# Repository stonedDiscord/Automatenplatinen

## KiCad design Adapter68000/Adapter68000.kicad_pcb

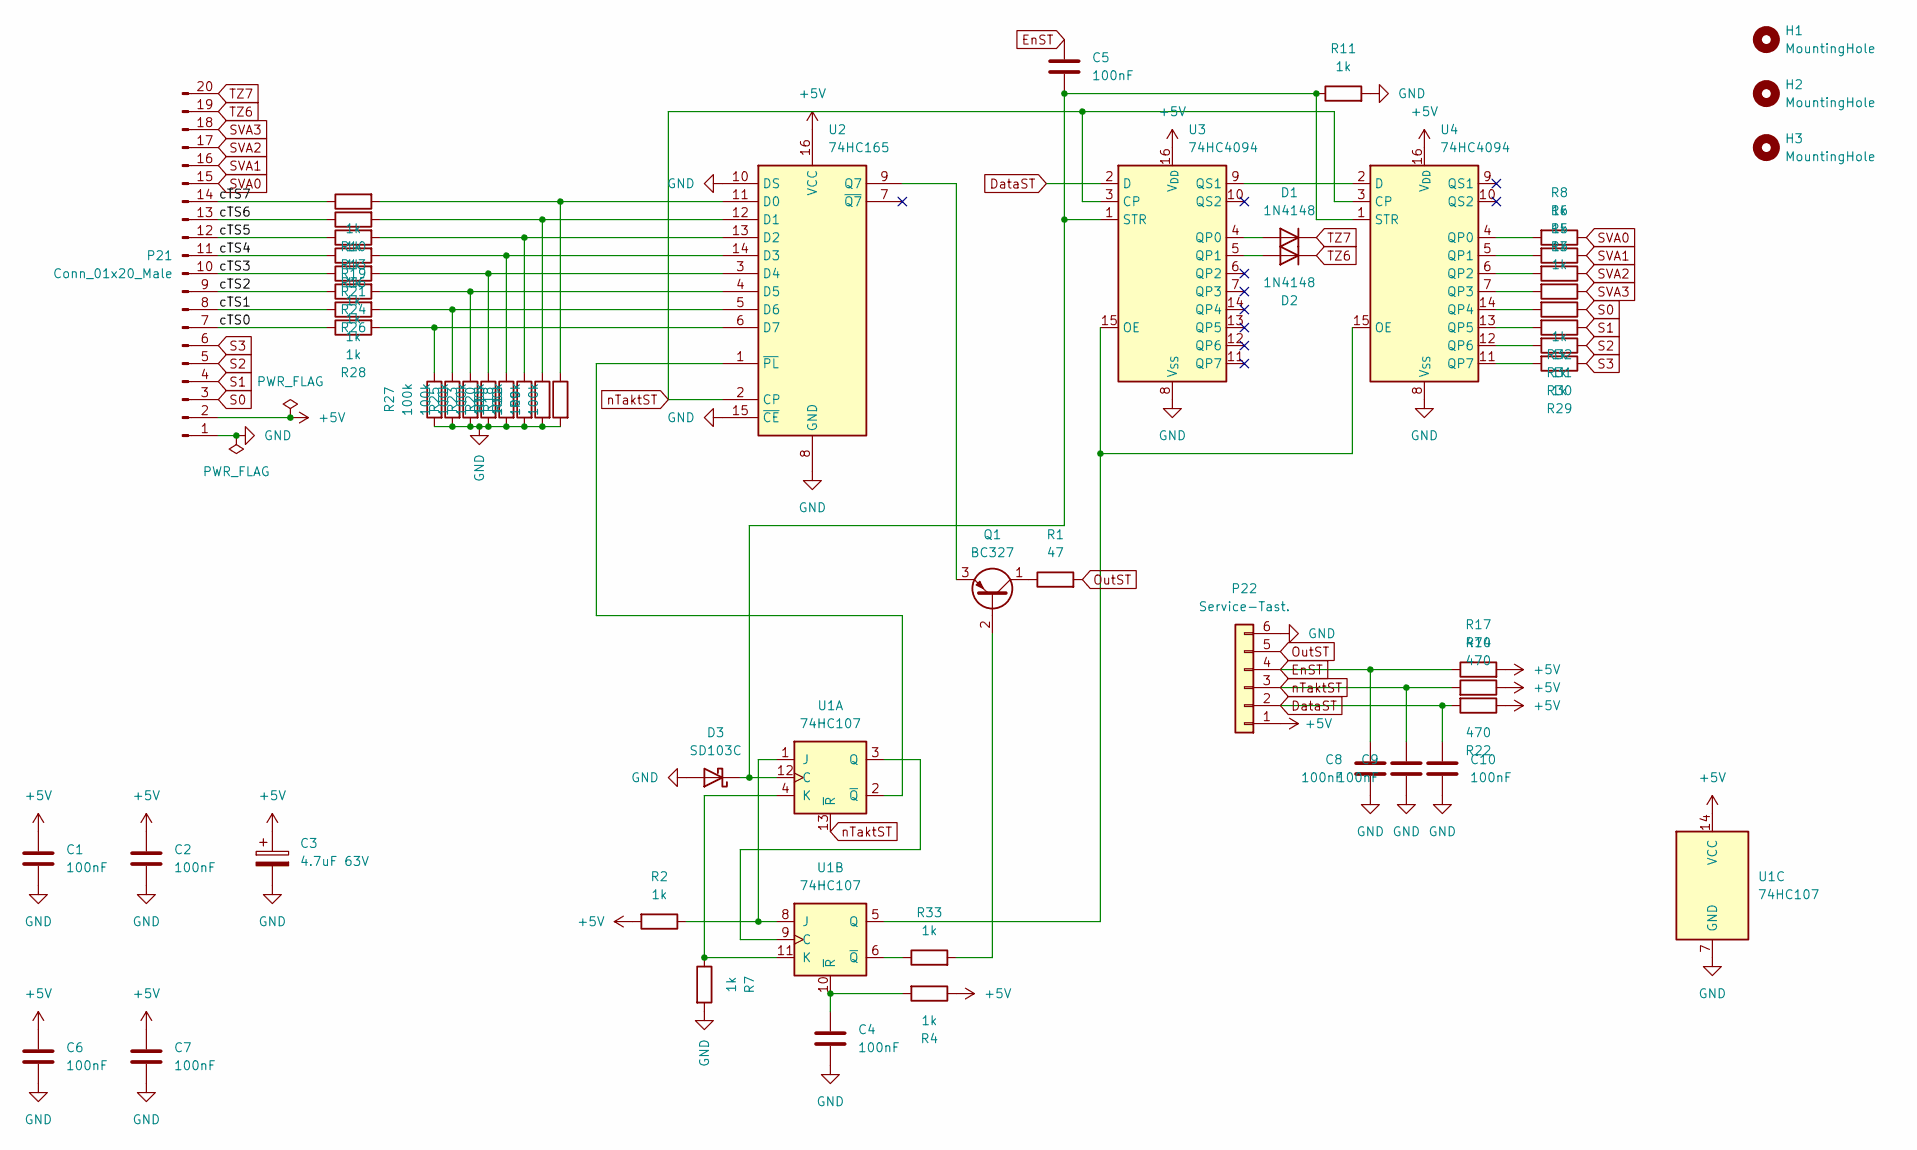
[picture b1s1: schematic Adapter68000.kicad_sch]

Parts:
C1, C2, C4, C5, C6, C7, C8, C9, C10: 100nF; C_Axial_L3.8mm_D2.6mm_P7.50mm_Horizontal
C3: 4.7uF 63V; CP_Axial_L11.0mm_D5.0mm_P18.00mm_Horizontal
D1, D2: 1N4148; D_DO-35_SOD27_P7.62mm_Horizontal
D3: SD103C; D_DO-35_SOD27_P7.62mm_Horizontal
H1, H2, H3: MountingHole; MountingHole_3.2mm_M3
P21: Conn_01x20_Male; Stocko_MKS_1670-6-0-2020_1x20_P2.50mm_Vertical
P22: Service-Tast.; Lumberg_MSF_B6B-MSF-A_1x06_P2.50mm_Vertical
Q1: BC327; TO-92
R1: 47; R_Axial_DIN0207_L6.3mm_D2.5mm_P10.16mm_Horizontal
R2, R3, R4, R5, R6, R7, R8, R10, R11, R13, R16, R19, R21, R24, R26, R28, R29, R30, R31, R32, R33: 1k; R_Axial_DIN0207_L6.3mm_D2.5mm_P10.16mm_Horizontal
R9, R12, R15, R18, R20, R23, R25, R27: 100k; R_Axial_DIN0207_L6.3mm_D2.5mm_P10.16mm_Horizontal
R14, R17, R22: 470; R_Axial_DIN0207_L6.3mm_D2.5mm_P10.16mm_Horizontal
U1: 74HC107; DIP-14_W7.62mm
U2: 74HC165; DIP-16_W7.62mm
U3, U4: 74HC4094; DIP-16_W7.62mm

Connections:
+5V: C1.2, C2.2, C3.1, C6.2, C7.2, P21.2, P22.1, R2.2, R4.1, R14.1, R17.2, R22.1, U1.14 (VCC), U2.16 (VCC), U3.16 (V_{DD}), U4.16 (V_{DD})
/cTS0: P21.7, R28.1
/cTS1: P21.8, R26.1
/cTS2: P21.9, R24.1
/cTS3: P21.10, R21.1
/cTS4: P21.11, R19.1
/cTS5: P21.12, R16.1
/cTS6: P21.13, R13.1
/cTS7: P21.14, R10.1
DataST: C10.2, P22.2, R22.2, U3.2 (D)
EnST: C5.2, C8.2, P22.4, R17.1
GND: C1.1, C2.1, C3.2, C4.1, C6.1, C7.1, C8.1, C9.1, C10.1, D3.2 (A), P21.1, P22.6, R7.2, R9.2, R11.2, R12.2, R15.2, R18.2, R20.2, R23.2, R25.2, R27.2, U1.7 (GND), U2.8 (GND), U2.10 (DS), U2.15 (~CE), U3.8 (V_{SS}), U4.8 (V_{SS})
unnamed: D1.2 (A), U3.4 (QP0)
unnamed: D2.2 (A), U3.5 (QP1)
unnamed: C5.1, D3.1 (K), R11.1, U1.12 (C), U3.1 (STR), U4.1 (STR)
unnamed: Q1.2 (B), R33.2
unnamed: Q1.1 (C), R1.1
unnamed: Q1.3 (E), U2.9 (Q7)
unnamed: R2.1, U1.1 (J), U1.8 (J)
unnamed: R7.1, U1.4 (K), U1.11 (K)
unnamed: U1.3 (Q), U1.9 (C)
unnamed: U1.2 (~Q), U2.1 (~PL)
unnamed: U1.5 (Q), U3.15 (OE), U4.15 (OE)
unnamed: R33.1, U1.6 (~Q)
unnamed: C4.2, R4.2, U1.10 (~R)
unnamed: R9.1, R10.2, U2.11 (D0)
unnamed: R12.1, R13.2, U2.12 (D1)
unnamed: R15.1, R16.2, U2.13 (D2)
unnamed: R18.1, R19.2, U2.14 (D3)
unnamed: R20.1, R21.2, U2.3 (D4)
unnamed: R23.1, R24.2, U2.4 (D5)
unnamed: R25.1, R26.2, U2.5 (D6)
unnamed: R27.1, R28.2, U2.6 (D7)
unnamed: U3.9 (QS1), U4.2 (D)
unnamed: R8.2, U4.4 (QP0)
unnamed: R6.2, U4.5 (QP1)
unnamed: R5.2, U4.6 (QP2)
unnamed: R3.2, U4.7 (QP3)
unnamed: R32.2, U4.14 (QP4)
unnamed: R31.2, U4.13 (QP5)
unnamed: R30.2, U4.12 (QP6)
unnamed: R29.2, U4.11 (QP7)
OutST: P22.5, R1.2
S0: P21.3, R32.1
S1: P21.4, R31.1
S2: P21.5, R30.1
S3: P21.6, R29.1
SVA0: P21.15, R8.1
SVA1: P21.16, R6.1
SVA2: P21.17, R5.1
SVA3: P21.18, R3.1
TZ6: D2.1 (K), P21.19
TZ7: D1.1 (K), P21.20
nTaktST: C9.2, P22.3, R14.2, U1.13 (~R), U2.2 (CP), U3.3 (CP), U4.3 (CP)

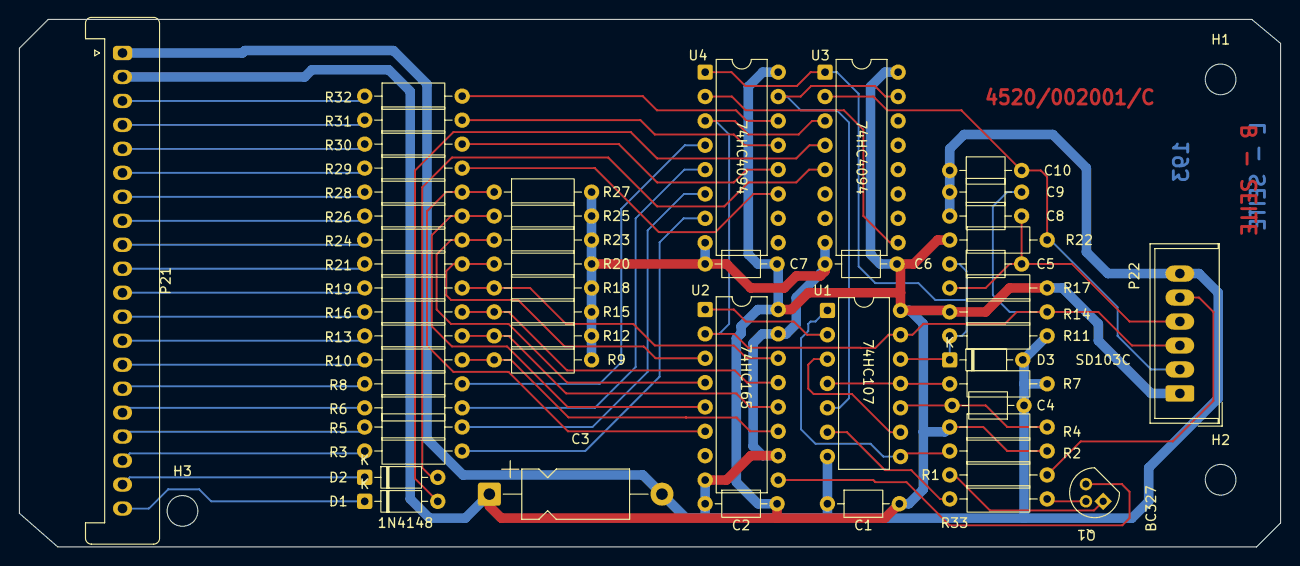
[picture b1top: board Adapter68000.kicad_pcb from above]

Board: 2 copper layers, 131.5 x 55.0 mm, 56 parts (0 on the bottom side), 54 nets.

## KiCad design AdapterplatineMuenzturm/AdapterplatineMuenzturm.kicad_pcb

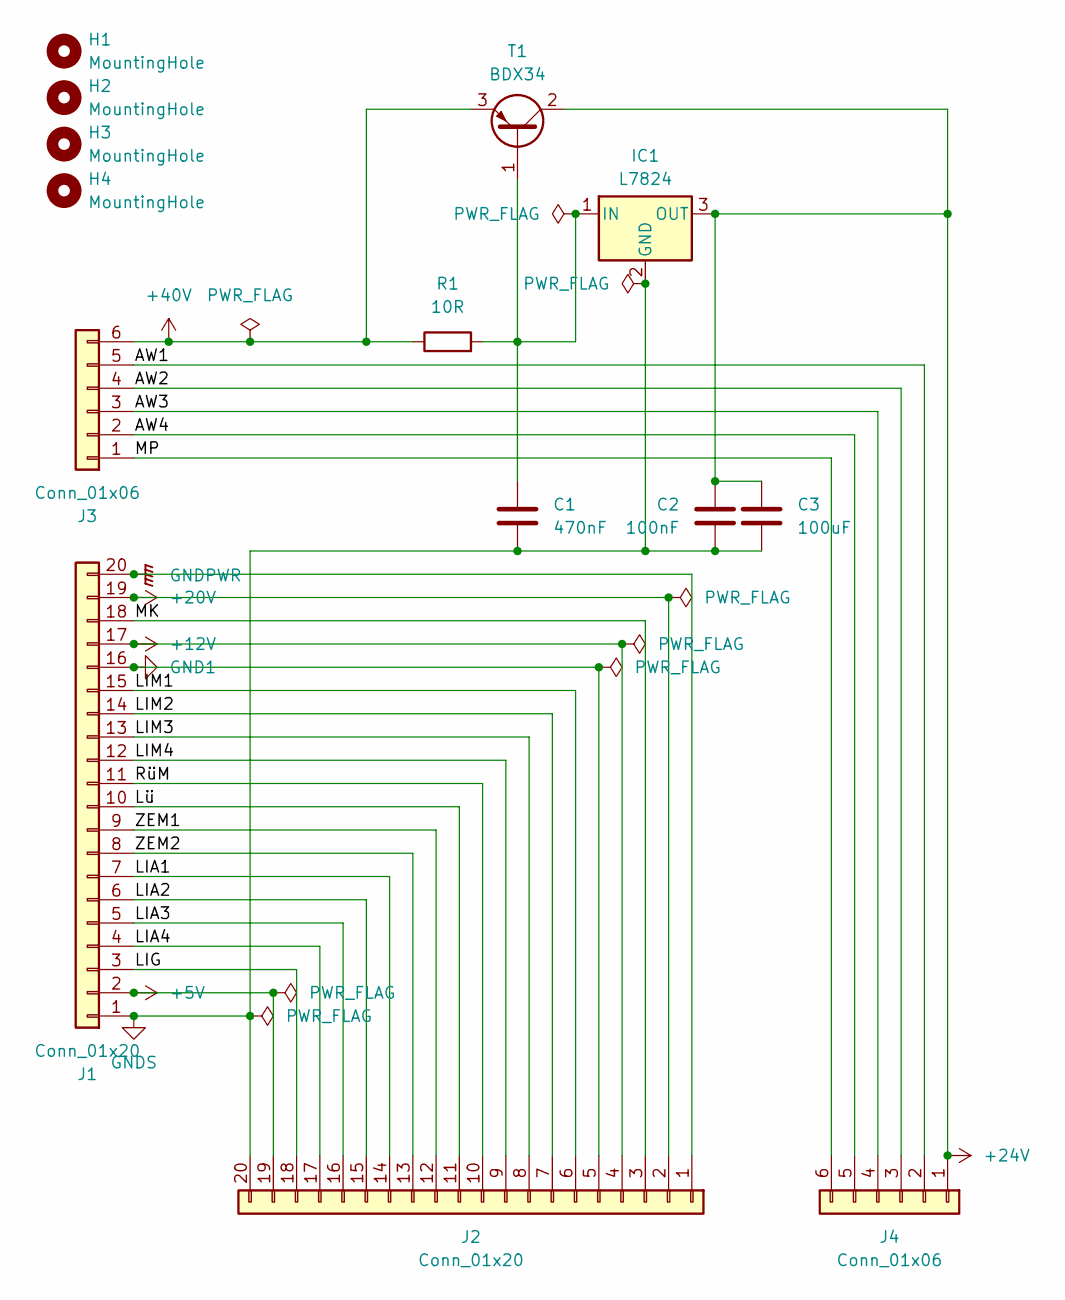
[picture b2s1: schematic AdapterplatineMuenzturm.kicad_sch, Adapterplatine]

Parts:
C1: 470nF; C_Rect_L7.0mm_W2.0mm_P5.00mm
C2: 100nF; C_Axial_L3.8mm_D2.6mm_P7.50mm_Horizontal
C3: 100uF; CP_Radial_D8.0mm_P5.00mm
H1, H2, H3, H4: MountingHole; MountingHole_2.2mm_M2
IC1: L7824; TO-220-3_Vertical
J1, J2: Conn_01x20; Stocko_MKS_1670-6-0-2020_1x20_P2.50mm_Vertical
J3, J4: Conn_01x06; Stocko_MKS_1656-6-0-606_1x6_P2.50mm_Vertical
R1: 10R; R_Axial_DIN0204_L3.6mm_D1.6mm_P7.62mm_Horizontal
T1: BDX34; TO-220-3_Horizontal_TabDown

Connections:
+5V: J1.2, J2.19
+12V: J1.17, J2.4
+20V: J1.19, J2.2
+24V: C2.1, C3.1, IC1.3 (OUT), J4.1, T1.2 (C)
+40V: J3.6, R1.1, T1.3 (E)
/AW1: J3.5, J4.2
/AW2: J3.4, J4.3
/AW3: J3.3, J4.4
/AW4: J3.2, J4.5
/LIA1: J1.7, J2.14
/LIA2: J1.6, J2.15
/LIA3: J1.5, J2.16
/LIA4: J1.4, J2.17
/LIG: J1.3, J2.18
/LIM1: J1.15, J2.6
/LIM2: J1.14, J2.7
/LIM3: J1.13, J2.8
/LIM4: J1.12, J2.9
/Lü: J1.10, J2.11
/MK: J1.18, J2.3
/MP: J3.1, J4.6
/RüM: J1.11, J2.10
/ZEM1: J1.9, J2.12
/ZEM2: J1.8, J2.13
GND1: J1.16, J2.5
GNDPWR: J1.20, J2.1
GNDS: C1.2, C2.2, C3.2, IC1.2 (GND), J1.1, J2.20
unnamed: C1.1, IC1.1 (IN), R1.2, T1.1 (B)

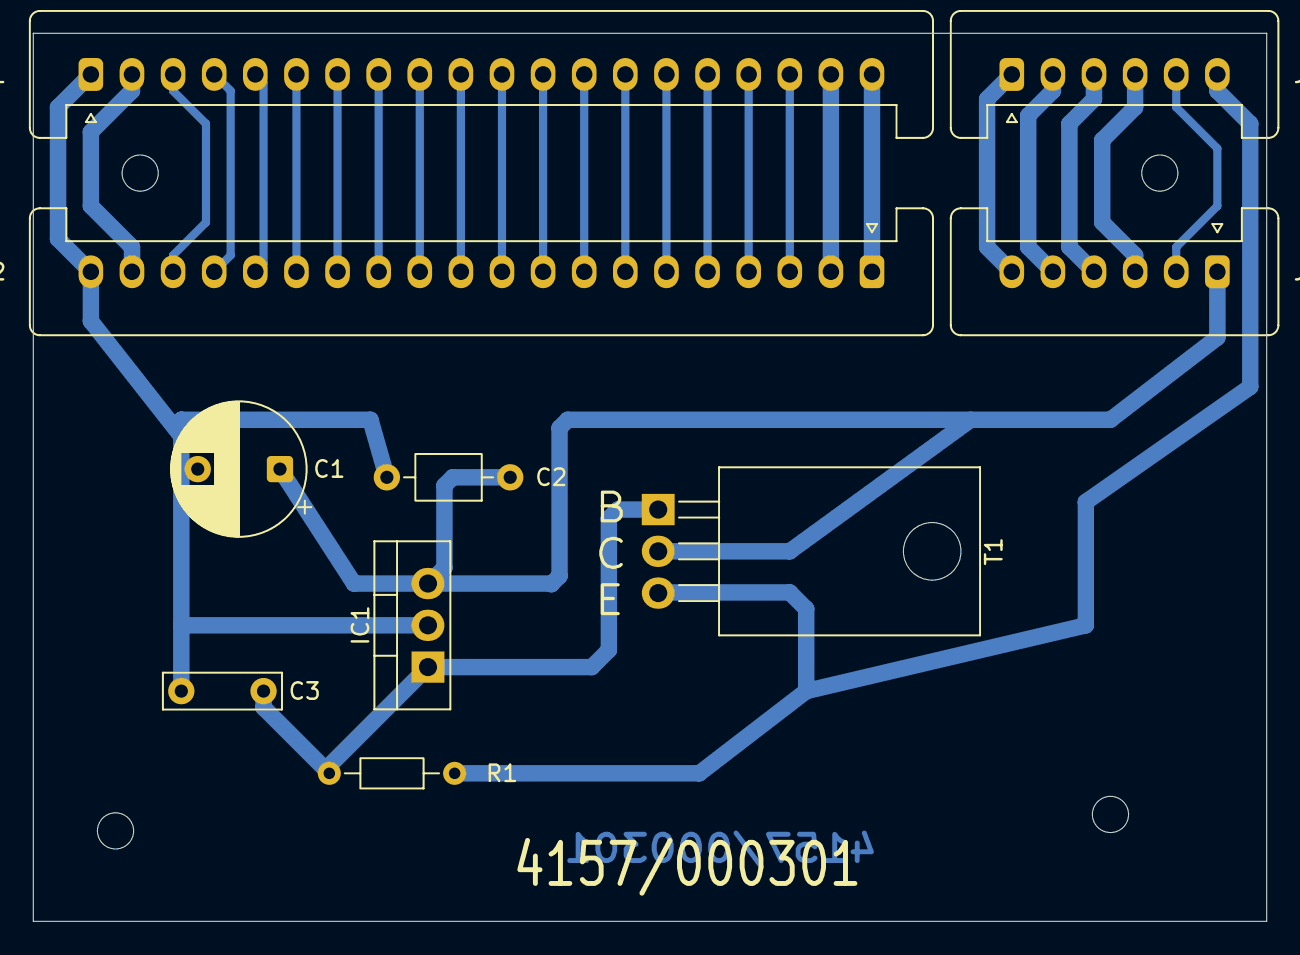
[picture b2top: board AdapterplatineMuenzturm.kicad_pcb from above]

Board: 2 copper layers, 75.0 x 54.0 mm, 14 parts (0 on the bottom side), 28 nets.

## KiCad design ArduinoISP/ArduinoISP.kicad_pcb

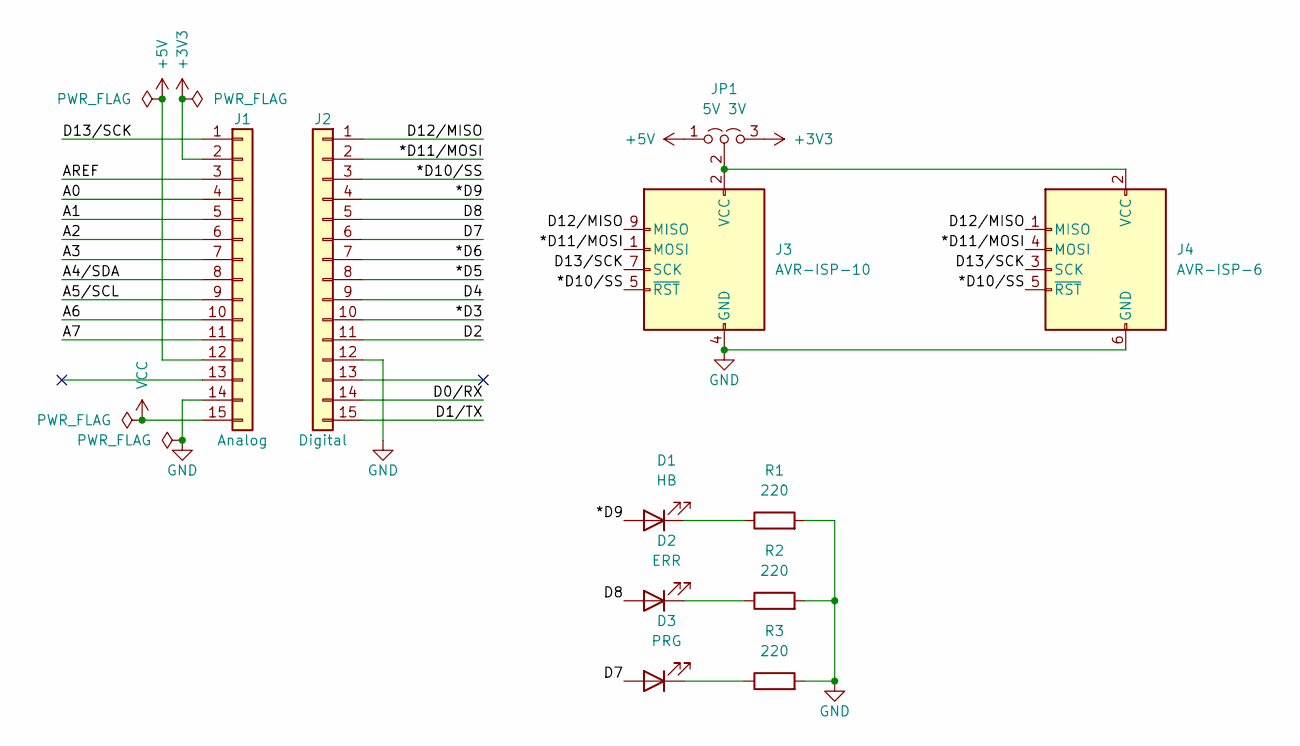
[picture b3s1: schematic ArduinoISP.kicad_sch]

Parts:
D1: HB; LED_0603_1608Metric_Pad1.05x0.95mm_HandSolder
D2: ERR; LED_0603_1608Metric_Pad1.05x0.95mm_HandSolder
D3: PRG; LED_0603_1608Metric_Pad1.05x0.95mm_HandSolder
J1: Analog; PinSocket_1x15_P2.54mm_Vertical
J2: Digital; PinSocket_1x15_P2.54mm_Vertical
J3: AVR-ISP-10; IDC-Header_2x05_P2.54mm_Vertical
J4: AVR-ISP-6; IDC-Header_2x03_P2.54mm_Horizontal
JP1: 5V 3V; PinHeader_1x03_P2.54mm_Vertical
R1, R2, R3: 220; R_0603_1608Metric_Pad0.98x0.95mm_HandSolder

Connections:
+3V3: J1.2, JP1.3 (B)
+5V: J1.12, JP1.1 (A)
/*D3: J2.10
/*D5: J2.8
/*D6: J2.7
/*D9: D1.2 (A), J2.4
/*D10/SS: J2.3, J3.5 (~RST), J4.5 (~RST)
/*D11/MOSI: J2.2, J3.1 (MOSI), J4.4 (MOSI)
/A0: J1.4
/A1: J1.5
/A2: J1.6
/A3: J1.7
/A4/SDA: J1.8
/A5/SCL: J1.9
/A6: J1.10
/A7: J1.11
/AREF: J1.3
/D0/RX: J2.14
/D1/TX: J2.15
/D2: J2.11
/D4: J2.9
/D7: D3.2 (A), J2.6
/D8: D2.2 (A), J2.5
/D12/MISO: J2.1, J3.9 (MISO), J4.1 (MISO)
/D13/SCK: J1.1, J3.7 (SCK), J4.3 (SCK)
GND: J1.14, J2.12, J3.4 (GND), J3.6 (GND), J3.8 (GND), J3.10 (GND), J4.6 (GND), R1.2, R2.2, R3.2
unnamed: D1.1 (K), R1.1
unnamed: D2.1 (K), R2.1
unnamed: D3.1 (K), R3.1
unnamed: J3.2 (VCC), J4.2 (VCC), JP1.2 (C)
VCC: J1.15

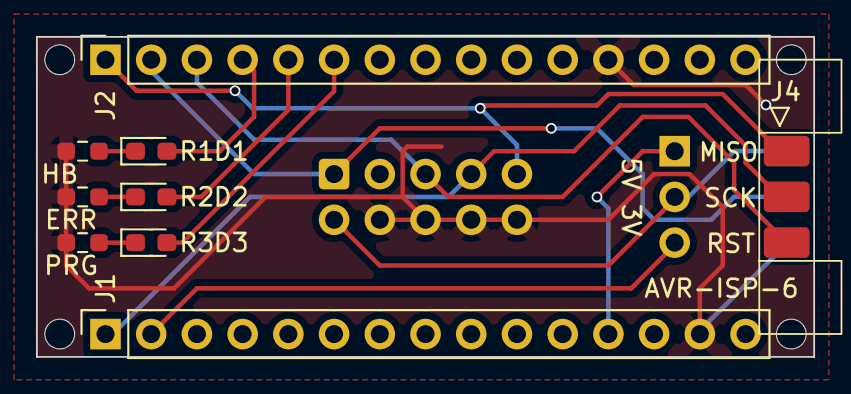
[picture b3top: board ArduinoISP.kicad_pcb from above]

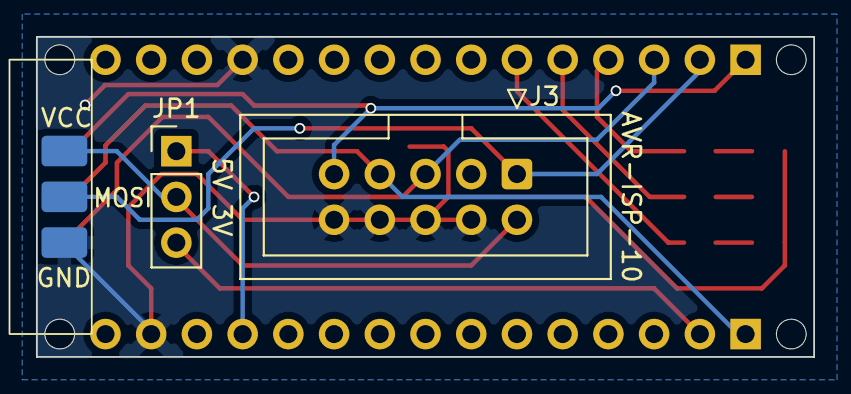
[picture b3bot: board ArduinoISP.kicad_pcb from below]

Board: 2 copper layers, 43.2 x 17.8 mm, 15 parts (2 on the bottom side), 14 nets.

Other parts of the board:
MH1, MH2, MH3, MH4: MountingHole_65mil
